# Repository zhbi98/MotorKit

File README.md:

## ODriveX

一款基于 STM32F405 的高性能开源磁场定向控制（FOC）驱动器，逆变电路采用了英飞凌的 DirectFET-MOS 管，支持高达 100A 持续电流 和 3kW 电机功率，适用于机器人、无人机、CNC 等高动态应用场景。

## 核心特性

(1) 高性能功率级：英飞凌 DirectFET MOSFET，60V 耐压，单路 100A 峰值电流

(2) 多总线通信：USB-CDC、UART、RS485（Modbus RTU）、CAN 2.0B

(3) 高精度反馈：支持 AS5047P（14-bit SPI）、ABI 编码器、UVW 霍尔

(4) 现代开发栈：CMake + ARM-GCC + VSCode + OpenOCD 图形化调试

(5) 完整 FOC 控制：电流/速度/位置三闭环，支持 SVPWM、死区补偿、弱磁控制

(6) Step/Dir 兼容：可对接传统运动控制器（如 GRBL、Marlin）

## 硬件

硬件涉及两部分，驱动器主体（驱动器硬件命名为 MotorKit）和编码器模块（AS5047P-Driver）。PCB 打样使用制造输出文件（Gerber），打样时把所有 Gerber 文件压缩为 .zip 文件提供给 PCB 制造商（例如嘉立创）即可，PCB 经过我打样验证无误，Gerber 文件在 HardWare/Gerber 目录下，可直接使用。

原理图和 PCB 使用开源 EDA 工具 KiCAD 设计的，如果你有 KiCAD 也知道怎么使用，可以自己去导出 Gerber 文件。

PCB 采用 4层板设计，如果要编辑 PCB 需要下载 KiCAD，还需要看些教程熟悉使用方法，当然这个 EDA 工具本身也非常易学。

购买电子元器件按照 HardWare 目录下的 ibom.html 表格购买。

KiCAD 官方下载链接： https://www.kicad.org/

驱动器主体 KiCAD 工程目录：HardWare/kiacd_project

编码器模块 KiCAD 工程目录：HardWare/AS5047P/HardWare/kiacd_project

制造输出文件（Gerber）目录：HardWare/Gerber

器件 BOM 目录：HardWare/ibom.html

## 固件

程序固件使用 CMake 进行构建的，然后用 ARM-GCC 进行编译的，并且可以搭配 VSCode 和 OpenOCD 进行图形化调试，当然你可以新建一个 STM32F405 的 Keil 工程，把程序组织到 Keil 中编译也可以。

使用 CMake 要求会编写 CMakeLists.txt 文件，不过我这里已经编写好了，在 Firmware 目录下可以看到。

PCB 上预留了 SWD 调试接口，固件固件就可以使用 SWD 下载。

如果没有 VSCode 的嵌入式开发环境，可以看看这篇文章：https://blog.csdn.net/jf_52001760/article/details/126826393

## 电机

我购买的无刷电机是大疆精灵 3 的拆机无刷电机 2312S 可以在淘宝搜索购买，电机到手后还要进行改装，在电机轴上安装供编码器检测的径向磁铁，磁铁尺寸为 6mmx2mm，磁铁安装注意同心度不要过度偏移，磁铁与编码器的间隙大概为 1.0mm。然后再把把 AS5047 编码器模块固定到电机尾部。

## Configuration

控制参数（例如 PID，电流，速度限制等等）都是包含默认值的，所以不需要逐个配置参数电机也能正常工作起来的，必须要注意的是根据实际编码器配置 cpr（例如 AS5047P 编码器使用 ABZ 接口时 CPR 为 1000x4=4000），index 参数，根据电机配置极对数 pole pairs（例如大疆 2312s 电机的极对数为 7），以及按实际调整电流采样电阻，配置一些必须变更的即可。

什么是极对数？

极数是指电机转子（即永磁体部分）磁场中磁极的总数量，磁极总数除以 2 就是极对数，极对数用 P 表示，每个极对包含一个北磁极 N 和一个南磁极 S。

## Start-up

(1) 电机校准（实际就是测量电机的相电阻和相电感）。

(2) 搜索定位编码器 index 信号（在编码器偏移校准之前必须先搜索 index）。

(3) 编码器偏移校准（Offset 校准）。

(4) 使能闭环状态/开环状态。

(5) 设置控制模式（控制模式包含：位置模式，速度模式，电流模式）。和 (4) 结合起来就得到，位置闭环控制模式，速度闭环控制模式，电流闭环控制模式。

(6) 设置控制模式目标值（位置值，速度值，电流值）来调节电机运行状态。

(7) 电机因异常停止后清除错误重新使能进入闭环状态即可。

## Command

CAN 通信协议和 Shell 交互命令实现分别位于 [communication/can/odrive_can.cpp](communication/can/odrive_can.cpp) 和 [ThirdParty/LetterShell/src/shell_cmd_list.c](ThirdParty/LetterShell/src/shell_cmd_list.c) 文件，具体可查看这两个文件，这里列出电机运行起来必要的 Shell 指令，使用 USB 数据线线连接板子 TypeC 和 PC，在 PC 上使用串口调试助手
下发下列指令即可控制。

```cpp
设置最大负电流
odrive:/$ dc_max_negative_current "-2.0"

速度限制 50 turn/s
odrive:/$ controller_config_vel_limit 0 "50.0"

设置电机 0 进入校准状态
odrive:/$ axis_requested_state 0 3

设置电机 0 进入力矩控制模式
odrive:/$ controller_config_control_mode 0 1

设置电机 0 控制力矩
odrive:/$ controller_input_torque 0 "0.02"

进入闭环
odrive:/$ axis_requested_state 0 8

打印当前错误
odrive:/$ dump_errors 1
```

## Step/Dir

Choose any two of the unused GPIOs for step/dir input. Let’s say you chose GPIO7 for the step signal and GPIO8 for the dir signal.

选择任意两个未使用的 GPIO 即可用于 step 和 dir 信号步骤/输入，假设您选择 GPIO7 作为步长信号，GPIO8 选择用于 dir 信号。

这种是基于 step 对应 GPIO 中断对外部电平输入步数累计（中断次数累计），达到位置控制信号可以通过普通 GPIO 输入的目的，

注意这不是 PWM 输入控制模式，两者是有区别的。

This is the simplest possible way of controlling the ODrive. It is also the most primitive and fragile one. So don’t use it unless you must interoperate with other hardware that you don’t control.

这是给驱动器提供控制指令信号最简单的方法。 它也是最原始且最脆弱的一个。因此,除非必须与其他无法控制的硬件进行互操作,否则请勿使用。

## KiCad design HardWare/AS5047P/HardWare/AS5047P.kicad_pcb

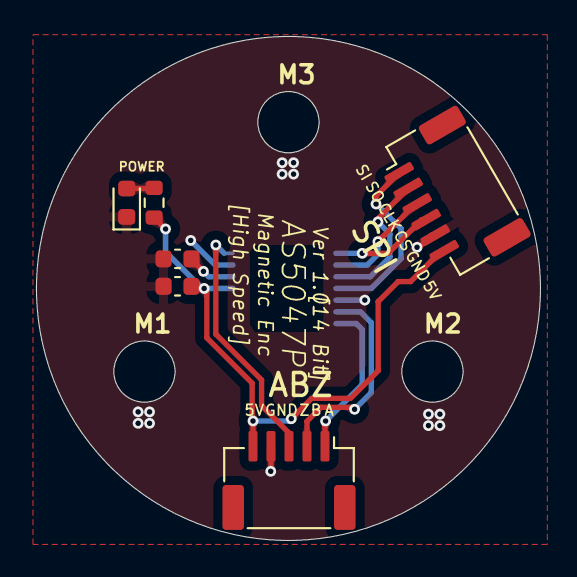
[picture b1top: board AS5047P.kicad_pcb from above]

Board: 2 copper layers, 28.0 x 28.0 mm, 7 parts (1 on the bottom side), 11 nets.

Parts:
C1: 0.1uF; C_0603_1608Metric
C2: 1uF; C_0603_1608Metric
D1: Yellow LED; LED_0603_1608Metric
J1: CONN_1x5P; CONN-SMD_1x5P-P1.0-H_WAFER-SH1.0-5PWB
J2: CONN_1x5P; CONN-SMD_1x6P-P1.0-H_WAFER-SH1.0-6PWB
R1: 1K; R_0603_1608Metric
U1: AS5047D; TSSOP-14_4.4x5mm_P0.65mm

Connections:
+5V: C1.2, J1.5, J2.6, R1.1, U1.11 (VDD)
/A: J1.1, U1.7 (A)
/B: J1.2, U1.6 (B)
/CLK: J2.3, U1.2 (CLK)
/CS: J2.4, U1.1 (~CS)
/MISO: J2.2, U1.3 (MISO)
/MOSI: J2.1, U1.4 (MOSI)
/Z: J1.3, U1.14 (I/PWM)
GND: C1.1, C2.2, D1.1 (K), J1.4, J2.5, U1.5 (TST), U1.13 (GND)
unnamed: D1.2 (A), R1.2
unnamed: C2.1, U1.12 (VDD3V3)

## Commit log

2025-11-16 硬件电路测试，添加数据手册，原理图，更新驱动器和 AS5047P 硬件设计
2025-11-17 添加Firmware文件
2025-11-17 移除测试程序，STM32中断函数统一放置到stm32f4xx_it文件，GPIO不命名
2025-11-17 移除Stm32SpiArbiter结构config配置定制字段，SPI统一配置(经过2x验证电机工作正常)
2025-11-17 中断处理使用HAL_GPIO_EXTI_IRQHandler，方便驱动替换((经过2x验证电机工作正常))
2025-11-17 PWM控制信号驱动修改通道GPIO指定方式（经过2x验证工作正常）
2025-11-17 Stm32SpiArbiter发送任务队列和Motor刹车配置逻辑整理（经过2x验证工作正常）
2025-11-17 移除多余函数接口，添加定时器寄存器配置说明，整理程序（经过2x验证工作正常）
2025-11-17 使用LetterShell替换LibFibre+Python实现命令控制，可不依赖Python脚本独立运行（经过2x验证工作正常）
2025-11-17 增加固件说明，解决USBD_CDC_DataOut调用Receive接口时没有向下传递hEP_Rx->Buffer导致CDC_Receive_FS获取Buf指针时为NULL导致接收数据为未知无效数据问题
2025-11-27 完成CAN接口和对应GPIO调试，增加Shell指令，增加CAN协议和控制指令，更新README文件（经过2x验证，工作正常）
2025-11-29 CAN协议增加位置速度，力位混控协议，电流/力矩反馈协议（经过2x验证，工作正常）
